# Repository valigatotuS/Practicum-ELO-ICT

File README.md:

# Practicum-ELO-ICT
3BA course, playing around with microcontrollers, fpga and many more
@ValentinQuevy @LoukaGrignard

## Summary 

This repository contains the final project for the cour "Practicum ELO-ICT", 
the goal of this is to drive an ledmatrix with the aid of Zynq2 FPGA, STM32 and other components.

The repo contains:
- VHDL test bench code
- PCB:
    - stm32 shield
    - external ledmatrixdriver
- STM32 test code

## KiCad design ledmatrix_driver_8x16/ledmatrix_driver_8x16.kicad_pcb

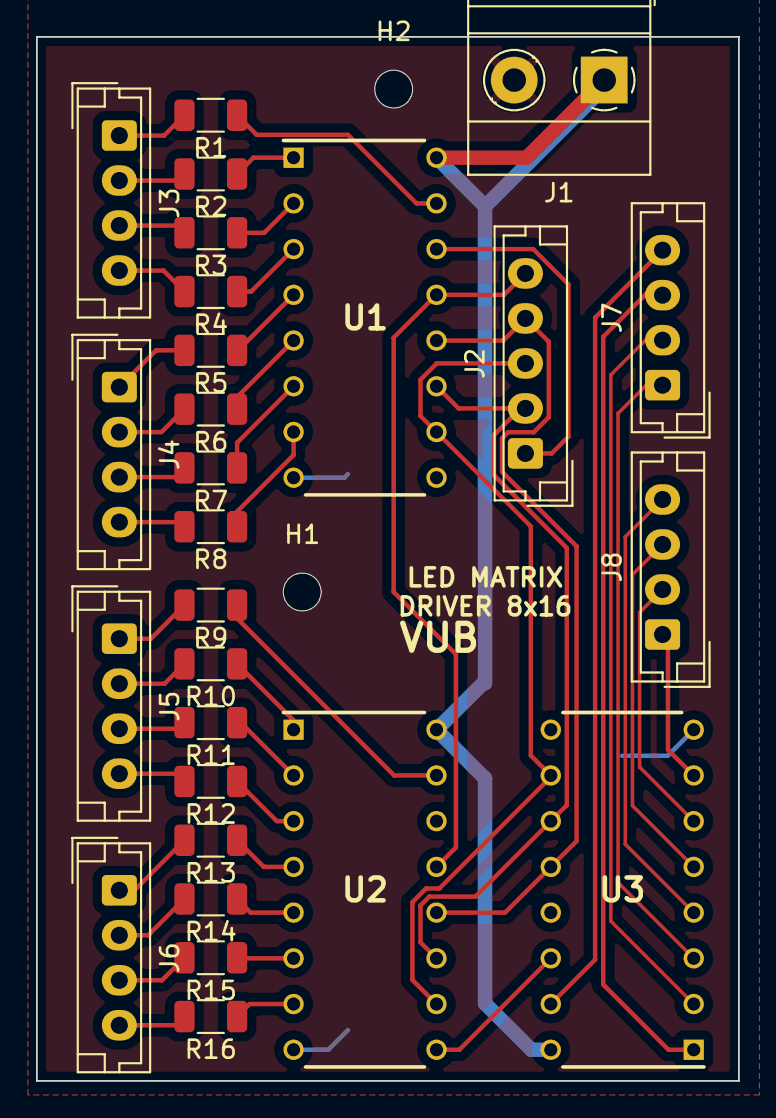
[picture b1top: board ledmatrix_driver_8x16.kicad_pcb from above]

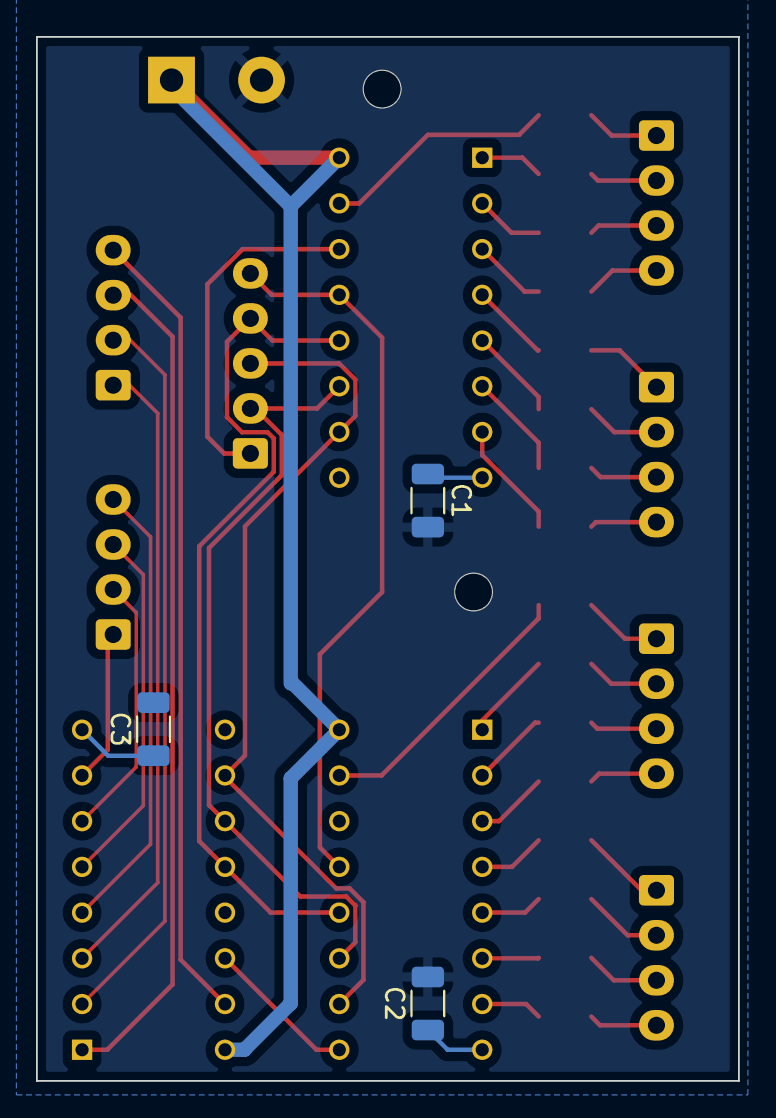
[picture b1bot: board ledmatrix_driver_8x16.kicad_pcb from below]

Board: 2 copper layers, 39.0 x 58.0 mm, 32 parts (3 on the bottom side), 49 nets.

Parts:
C1, C2, C3: 10uF; C_1206_3216Metric
H1, H2: MountingHole; MountingHole_2.1mm
J1: POWER; TerminalBlock_Phoenix_MKDS-1,5-2_1x02_P5.00mm_Horizontal
J2: SHIFT; JST_EH_B5B-EH-A_1x05_P2.50mm_Vertical
J3: COL_1-4; JST_EH_B4B-EH-A_1x04_P2.50mm_Vertical
J4: COL_5-8; JST_EH_B4B-EH-A_1x04_P2.50mm_Vertical
J5: COL_9-12; JST_EH_B4B-EH-A_1x04_P2.50mm_Vertical
J6: COL_13-16; JST_EH_B4B-EH-A_1x04_P2.50mm_Vertical
J7: ROW_1-4; JST_EH_B4B-EH-A_1x04_P2.50mm_Vertical
J8: ROW_5-8; JST_EH_B4B-EH-A_1x04_P2.50mm_Vertical
R1, R2, R3, R4, R5, R6, R7, R8, R9, R10, R11, R12, R13, R14, R15, R16: R300; R_1206_3216Metric
U1, U2, U3: 74HC595; DIP794W53P254L1930H508Q16N

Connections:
/COL3: J3.3, R3.2
/COL4: J3.4, R4.2
/COL6: J4.2, R6.2
/COL7: J4.3, R7.2
/COL8: J4.4, R8.2
/COL9: J5.1, R9.2
/COL10: J5.2, R10.2
/COL11: J5.3, R11.2
/COL12: J5.4, R12.2
/COL13: J6.1, R13.2
/COL14: J6.2, R14.2
/COL15: J6.3, R15.2
/COL16: J6.4, R16.2
/OE1: J2.5, U1.13 (~OE), U2.13 (~OE)
/RCLK1: J2.4, U1.12 (RCLK), U2.12 (RCLK), U3.12 (RCLK)
/ROW1: J7.4, U3.15 (QA)
/ROW2: J7.3, U3.1 (QB)
/ROW3: J7.2, U3.2 (QC)
/ROW4: J7.1, U3.3 (QD)
/ROW5: J8.4, U3.4 (QE)
/ROW6: J8.3, U3.5 (QF)
/ROW7: J8.2, U3.6 (QG)
/ROW8: J8.1, U3.7 (QH)
/SER1: J2.1, U1.14 (SER)
/SER1_B: U1.9 (QH'), U2.14 (SER)
/SER_ROWS: U2.9 (QH'), U3.14 (SER)
/SRCLK1: J2.2, U1.11 (SRCLK), U2.11 (SRCLK), U3.11 (SRCLK)
/SRCLR1: J2.3, U1.10 (~SRCLR), U2.10 (~SRCLR), U3.10 (~SRCLR)
GND: C1.2, C2.2, C3.2, J1.2
unnamed: C1.1, U1.8 (GND)
unnamed: C2.1, U2.8 (GND)
unnamed: C3.1, U3.8 (GND)
unnamed: R1.1, U1.15 (QA)
unnamed: R2.1, U1.1 (QB)
unnamed: R3.1, U1.2 (QC)
unnamed: R4.1, U1.3 (QD)
unnamed: R5.1, U1.4 (QE)
unnamed: R6.1, U1.5 (QF)
unnamed: R7.1, U1.6 (QG)
unnamed: R8.1, U1.7 (QH)
unnamed: R9.1, U2.15 (QA)
unnamed: R10.1, U2.1 (QB)
unnamed: R11.1, U2.2 (QC)
unnamed: R12.1, U2.3 (QD)
unnamed: R13.1, U2.4 (QE)
unnamed: R14.1, U2.5 (QF)
unnamed: R15.1, U2.6 (QG)
unnamed: R16.1, U2.7 (QH)
VCC: J1.1, U1.16 (VCC), U2.16 (VCC), U3.16 (VCC)

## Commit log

2022-02-21 add schematc
2022-06-23 VHDL code
2022-06-23 add ledmatrix driver
2022-06-23 add folder PCBs
2022-06-23 add folder sandbox
2022-06-24 add stm32 code
2022-06-24 add stm32 shield
